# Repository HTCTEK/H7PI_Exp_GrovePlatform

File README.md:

# H7PI_Exp_GrovePlatform

### What is H7PI_Exp_GrovePlatform
An expansion board for H7PI(STM32H7) users who are used to developing on Grove, such as light sensor, temperature sensor and so on.

### How to use
1. Buy Grove modules that you want to develop with.
2. Buy a H7PI_Exp_GrovePlatform and install H7PI on it.
3. Download H7PI_Samples and load Grove drivers.
4. Compile the project and download axf wiht mdk keil.
5. wiki-->[click]().

### Pictures

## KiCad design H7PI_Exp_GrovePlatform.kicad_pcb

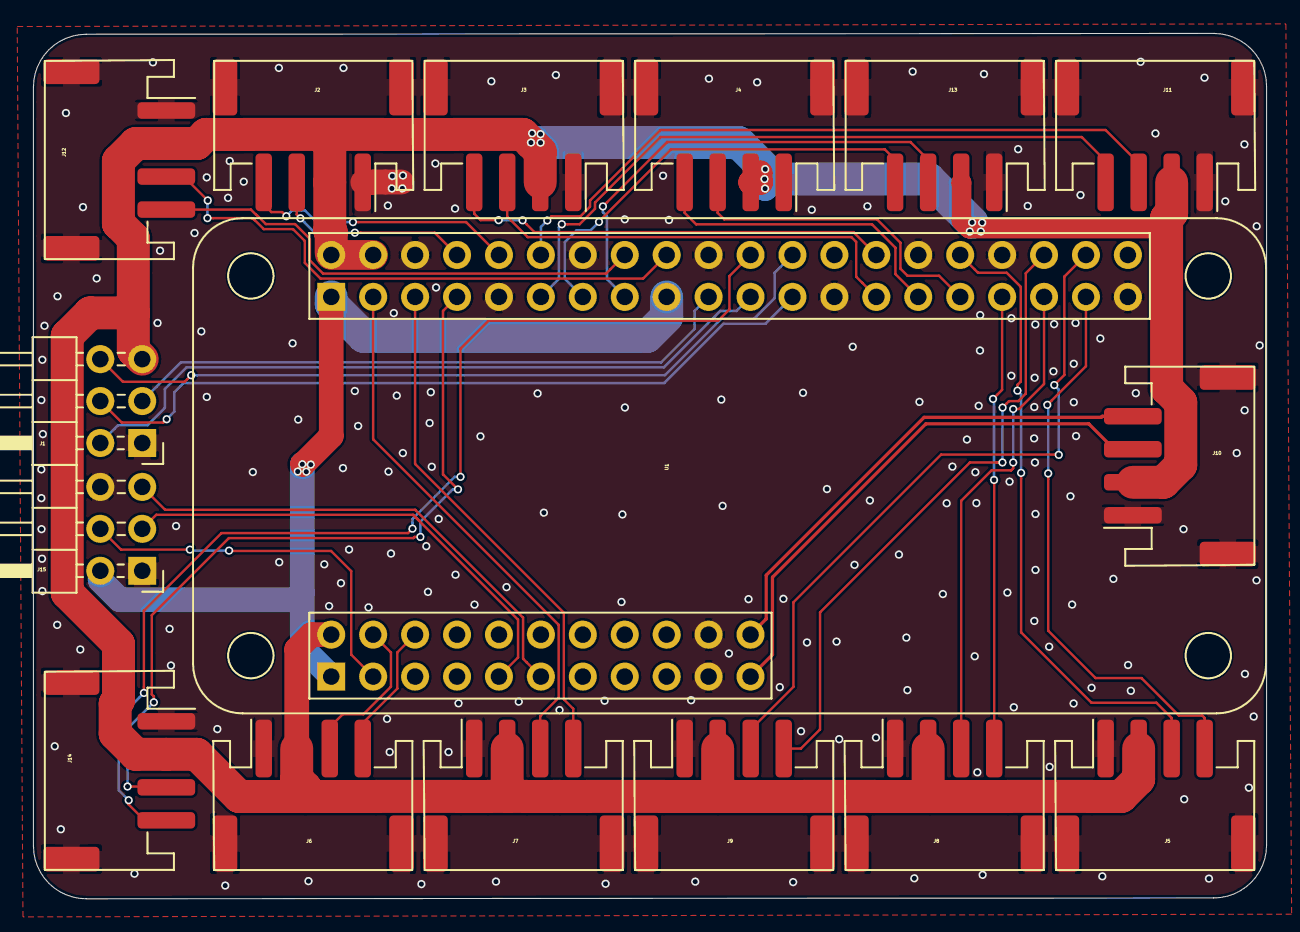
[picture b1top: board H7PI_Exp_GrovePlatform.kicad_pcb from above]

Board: 2 copper layers, 74.7 x 52.4 mm, 16 parts (0 on the bottom side), 36 nets.

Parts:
J1, J15: Header_2x3; PinHeader_2x03_P2.54mm_Horizontal
J2, J3, J4, J5, J6, J7, J8, J9, J10, J11, J12, J13, J14: A2001WR-S-4P; Connector_CJT_A2001WR-S-4P_1x04-1MP_P2.00mm_Horizontal
U1: H7PI_Exp; Module_H7PI_Exp_65x30mm

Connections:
/3V3: J15.2, U1.1, U1.21, U1.37
/A0: J4.4, U1.49
/A1: J4.3, U1.51
/A2: J8.4, U1.53
/A3: J8.3, U1.55
/A4: J5.4, U1.57
/A5: J5.3, U1.52
/A6: J9.4, U1.56
/A7: J9.3, U1.58
/BOOT: J15.4, U1.3
/CE0: J1.6, U1.44
/D0: J11.4, U1.31
/D1: J11.3, U1.32
/D2: J13.4, U1.33
/D3: J13.3, U1.35
/D4: J12.4, U1.36
/D5: J12.3, U1.38
/D6: J14.4, U1.42
/D7: J14.3, U1.27
/GND: J1.1, J2.1, J2.MP, J3.1, J3.MP, J4.1, J4.MP, J5.1, J5.MP, J6.1, J6.MP, J7.1, J7.MP, J8.1, J8.MP, J9.1, J9.MP, J10.1, J10.MP, J11.1, J11.MP, J12.1, J12.MP, J13.1, J13.MP, J14.1, J14.MP, J15.1, J15.6, U1.19, U1.20, U1.26, U1.29, U1.34, U1.40, U1.45, U1.50, U1.54, U1.59
/MISO: J1.2, U1.41
/MOSI: J1.3, U1.39
/RX0: J2.4, U1.30
/RX1: J6.4, U1.6
/SCK: J1.4, U1.43
/SCL0: J3.4, U1.48
/SCL1: J7.4, U1.25
/SDA0: J3.3, U1.47
/SDA1: J7.3, U1.23
/SWDCLK: J15.5, U1.11
/SWDIO: J15.3, U1.9
/TX0: J2.3, U1.28
/TX1: J6.3, U1.4
/USBN: J10.3, U1.USBN
/USBP: J10.4, U1.USBP
/VBUS: J1.5, J2.2, J3.2, J4.2, J5.2, J6.2, J7.2, J8.2, J9.2, J10.2, J11.2, J12.2, J13.2, J14.2, U1.2, U1.22, U1.24

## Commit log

2020-01-08 v0.1 push
2020-01-08 更新readme和pic
2020-01-09 add LICENSE BSD
